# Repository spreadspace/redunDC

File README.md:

redunDC
=======

A redundant DC power supply with UPS functionality based on Meanwell Powersupplies (PSC-x).

License
-------

redunDC is licensed under CERN OHL v.1.2 or later.
See LICENSE for details.

> Copyright CERN 2013.
>
> This documentation describes Open Hardware and is licensed under the
> CERN OHL v. 1.2.
>
> You may redistribute and modify this documentation under the terms of the
> CERN OHL v.1.2. (http://ohwr.org/cernohl). This documentation is distributed
> WITHOUT ANY EXPRESS OR IMPLIED WARRANTY, INCLUDING OF
> MERCHANTABILITY, SATISFACTORY QUALITY AND FITNESS FOR A
> PARTICULAR PURPOSE. Please see the CERN OHL v.1.2 for applicable
> conditions

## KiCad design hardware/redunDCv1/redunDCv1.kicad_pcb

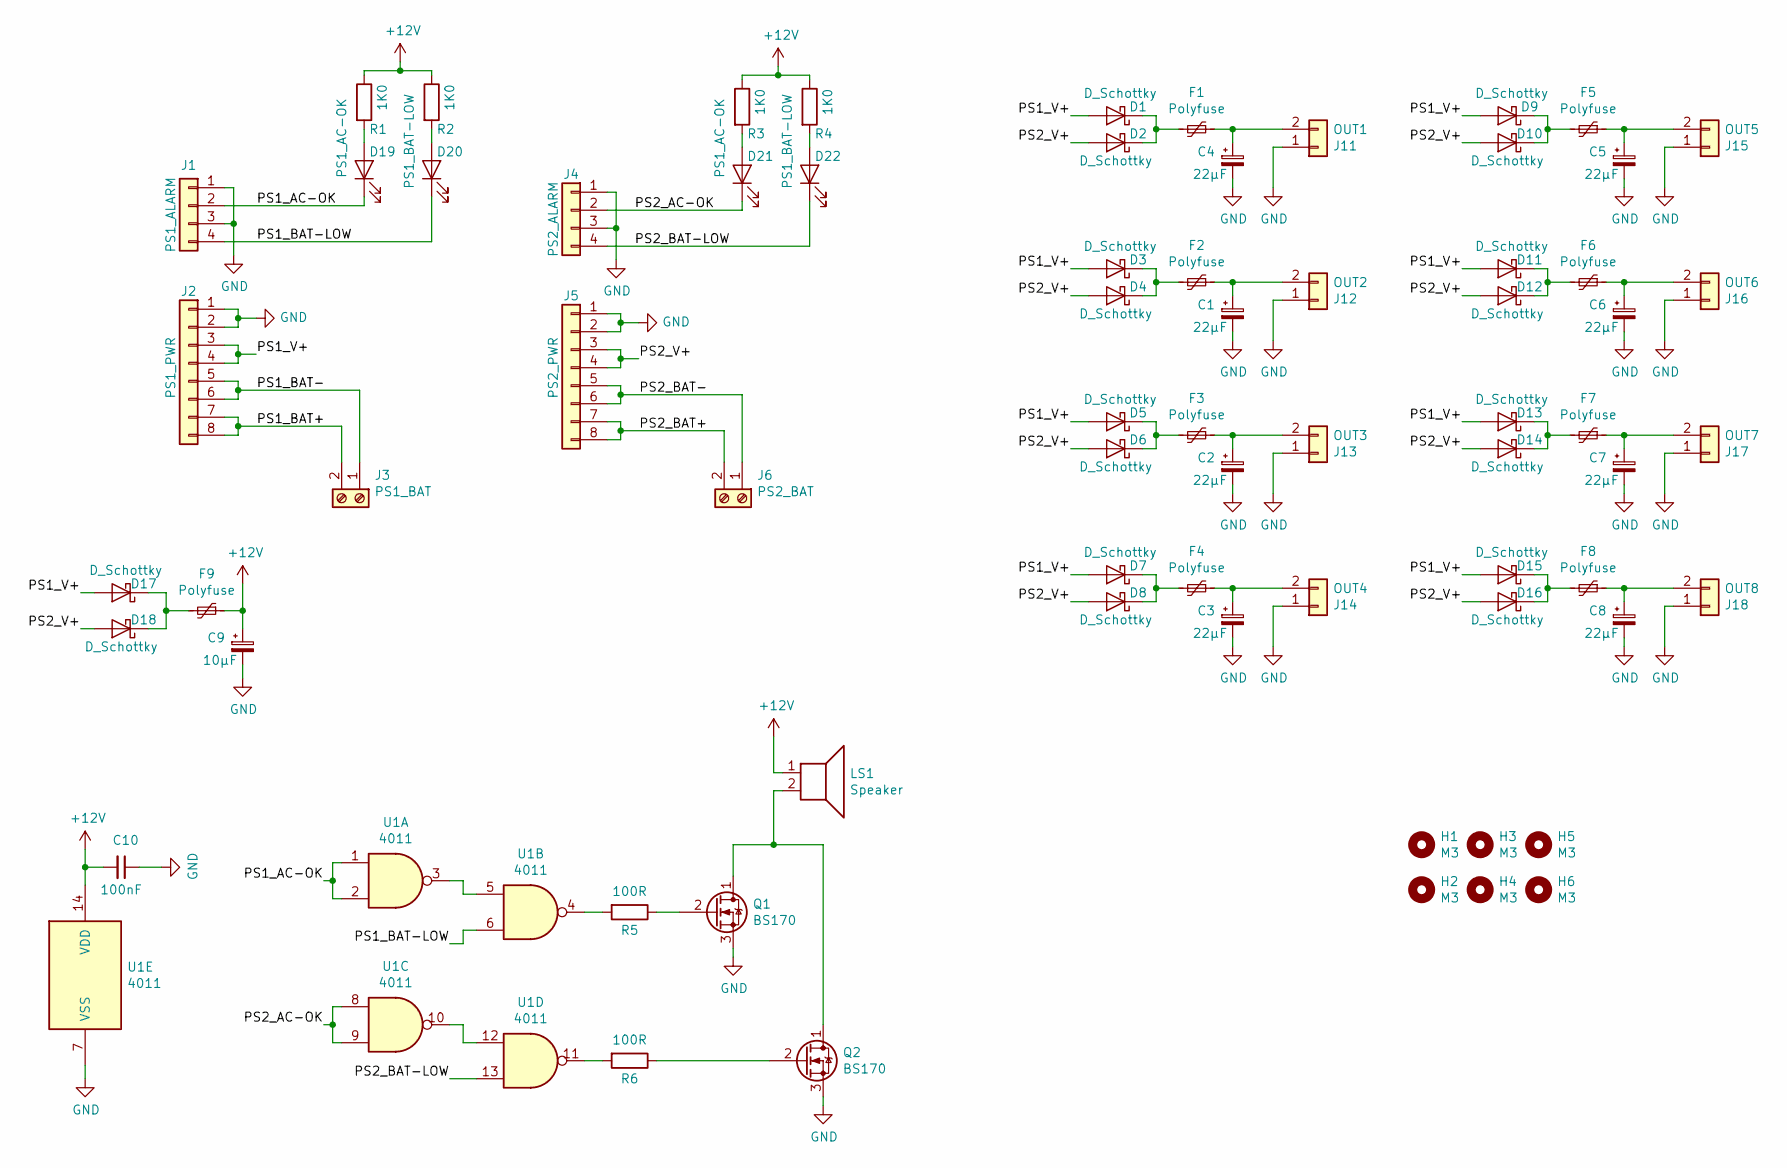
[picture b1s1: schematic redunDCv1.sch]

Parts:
C1, C2, C3, C4, C5, C6, C7, C8: 22µF; CP_EIA-7361-438_AVX-U
C9: 10µF; CP_EIA-6032-15_Kemet-U
C10: 100nF; C_0805_2012Metric
D1, D2, D3, D4, D5, D6, D7, D8, D9, D10, D11, D12, D13, D14, D15, D16, D17, D18: D_Schottky; D_1210_3225Metric
D19, D21: PS1_AC-OK; LED_D3.0mm
D20, D22: PS1_BAT-LOW; LED_D3.0mm
F1, F2, F3, F4, F5, F6, F7, F8, F9: Polyfuse; Fuse_1210_3225Metric
H1, H2, H3, H4, H5, H6: M3; MountingHole_3.2mm_M3
J1: PS1_ALARM; JST_XH_B4B-XH-A_1x04_P2.50mm_Vertical
J2: PS1_PWR; JST_VH_B8P-VH_1x08_P3.96mm_Vertical
J3: PS1_BAT; TerminalBlock_Altech_AK300-2_P5.00mm
J4: PS2_ALARM; JST_XH_B4B-XH-A_1x04_P2.50mm_Vertical
J5: PS2_PWR; JST_VH_B8P-VH_1x08_P3.96mm_Vertical
J6: PS2_BAT; TerminalBlock_Altech_AK300-2_P5.00mm
J11: OUT1; TerminalBlock_Wuerth_691311400102_P7.62mm
J12: OUT2; TerminalBlock_Wuerth_691311400102_P7.62mm
J13: OUT3; TerminalBlock_Wuerth_691311400102_P7.62mm
J14: OUT4; TerminalBlock_Wuerth_691311400102_P7.62mm
J15: OUT5; TerminalBlock_Wuerth_691311400102_P7.62mm
J16: OUT6; TerminalBlock_Wuerth_691311400102_P7.62mm
J17: OUT7; TerminalBlock_Wuerth_691311400102_P7.62mm
J18: OUT8; TerminalBlock_Wuerth_691311400102_P7.62mm
LS1: Speaker; Buzzer_15x7.5RM7.6
Q1, Q2: BS170; TO-92_Inline
R1, R2, R3, R4: 1K0; R_0805_2012Metric
R5, R6: 100R; R_0805_2012Metric
U1: 4011; SOIC-14_3.9x8.7mm_P1.27mm

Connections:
+12V: C9.1, C10.2, F9.1, LS1.1, R1.1, R2.1, R3.1, R4.1, U1.14 (VDD)
/PS1_AC-OK: D19.1 (K), J1.2, U1.1, U1.2
/PS1_BAT+: J2.7, J2.8, J3.2
/PS1_BAT-: J2.5, J2.6, J3.1
/PS1_BAT-LOW: D20.1 (K), J1.4, U1.6
/PS1_V+: D1.2 (A), D3.2 (A), D5.2 (A), D7.2 (A), D9.2 (A), D11.2 (A), D13.2 (A), D15.2 (A), D17.2 (A), J2.3, J2.4
/PS2_AC-OK: D21.1 (K), J4.2, U1.8, U1.9
/PS2_BAT+: J5.7, J5.8, J6.2
/PS2_BAT-: J5.5, J5.6, J6.1
/PS2_BAT-LOW: D22.1 (K), J4.4, U1.13
/PS2_V+: D2.2 (A), D4.2 (A), D6.2 (A), D8.2 (A), D10.2 (A), D12.2 (A), D14.2 (A), D16.2 (A), D18.2 (A), J5.3, J5.4
GND: C1.2, C2.2, C3.2, C4.2, C5.2, C6.2, C7.2, C8.2, C9.2, C10.1, J1.1, J1.3, J2.1, J2.2, J4.1, J4.3, J5.1, J5.2, J11.1, J12.1, J13.1, J14.1, J15.1, J16.1, J17.1, J18.1, Q1.3 (S), Q2.3 (S), U1.7 (VSS)
unnamed: C1.1, F2.1, J12.2
unnamed: C2.1, F3.1, J13.2
unnamed: C3.1, F4.1, J14.2
unnamed: C4.1, F1.1, J11.2
unnamed: C5.1, F5.1, J15.2
unnamed: C6.1, F6.1, J16.2
unnamed: C7.1, F7.1, J17.2
unnamed: C8.1, F8.1, J18.2
unnamed: D1.1 (K), D2.1 (K), F1.2
unnamed: D3.1 (K), D4.1 (K), F2.2
unnamed: D5.1 (K), D6.1 (K), F3.2
unnamed: D7.1 (K), D8.1 (K), F4.2
unnamed: D9.1 (K), D10.1 (K), F5.2
unnamed: D11.1 (K), D12.1 (K), F6.2
unnamed: D13.1 (K), D14.1 (K), F7.2
unnamed: D15.1 (K), D16.1 (K), F8.2
unnamed: D17.1 (K), D18.1 (K), F9.2
unnamed: D19.2 (A), R1.2
unnamed: D20.2 (A), R2.2
unnamed: D21.2 (A), R3.2
unnamed: D22.2 (A), R4.2
unnamed: LS1.2, Q1.1 (D), Q2.1 (D)
unnamed: Q1.2 (G), R5.1
unnamed: Q2.2 (G), R6.1
unnamed: R5.2, U1.4
unnamed: R6.2, U1.11
unnamed: U1.3, U1.5
unnamed: U1.10, U1.12

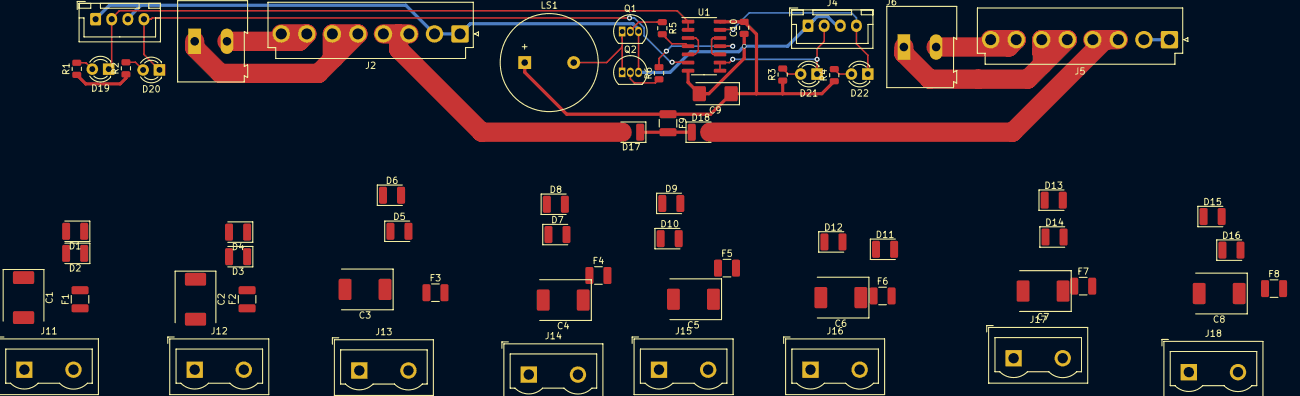
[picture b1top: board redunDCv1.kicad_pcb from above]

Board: 2 copper layers, 71 parts (0 on the bottom side), 40 nets.

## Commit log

2019-06-19 added most connectors
2019-06-19 first miniamal schematic is done
2019-06-19 initial footprint assignments (WIP)
2019-06-26 some routing tests...
2019-06-26 added mcu (WIP)
2019-06-30 added symbols for isolators
2019-07-17 schemativ almost done
